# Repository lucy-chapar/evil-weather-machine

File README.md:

# Evil Weather Machine

A carrier PCB and new firmware for the [PrintKits Digital Sand kit](https://printkits.com/blogs/instructions/digital-sand):
an ESP32 DevKit, a GY-521 accelerometer, an 8x8 WS2812B panel and a 4xAA box in a printed cube.

| | |
|---|---|
| [`pcb/`](pcb/) | KiCad 7 two-layer board (52 × 59.5 mm) that replaces the kit's point-to-point wiring, with Gerbers ready to order |
| [`firmware/weather/`](firmware/weather/) | ESP32 firmware: today's weather plus an injection-day reminder, with WiFi setup from a phone and updates over WiFi |

## Firmware

The panel flips through the current temperature, an animated icon for the weather right now (the moon in
its current phase at night), today's high and low, and the chance of rain when rain is likely in the next
12 hours. On injection days it adds a beating trans-flag heart, with a green dot in the corner for the
side to use.

### Shot day

A reminder for injectable estradiol (HRT).

**Schedule**
- One injection every 3 days: 10 injections in any 30-day window.
- The site alternates between the left and right side of the abdomen.
- Shot days are calculated from the calendar. Nothing is logged on the device.

**Display**
- On a shot day, one extra screen is added to the rotation, after the rain chance.
- It shows a heart in trans flag colours (blue, pink, white), beating, with white sparkle pixels around it.
- A green 2×2 dot in the bottom-left or bottom-right corner marks the injection side: left or right.
- On other days the screen is not shown.

**Configuration** ([`config.h`](firmware/weather/src/config.h))
- `LAST_SHOT_YEAR`, `LAST_SHOT_MONTH`, `LAST_SHOT_DAY`: the date of one injection to count from.
- `LAST_SHOT_SIDE`: the side of that injection, `'L'` or `'R'`.
- `SHOT_EVERY_DAYS`: the interval, 3 by default.
- If an injection is taken on a different day, the schedule does not adjust by itself. Set the values
  above to the most recent injection and update the firmware.

**Timekeeping**
- The date comes from internet time (NTP), in the local timezone reported by the weather service.
- After the first successful connection, the timezone is stored and the count continues without WiFi.
  Internet time is still needed after each power cycle.

Quick start, with [PlatformIO](https://platformio.org/) installed:

```bash
cd firmware/weather
pio run -t upload          # first time, over USB
pio run -e ota -t upload   # after that, over WiFi
```

On first boot, join the `DigitalSand-Weather` WiFi network from a phone to connect the toy to your WiFi.
Settings (units, panel orientation, shot schedule) are in
[`firmware/weather/src/config.h`](firmware/weather/src/config.h). See the
[firmware README](firmware/weather/README.md) for details.

## PCB

The board carries the ESP32 (either 0.9 in or 1.0 in header spacing), the GY-521, the button and screw
terminals for the battery and the LED panel. It's generated by
[`pcb/tools/generate_kicad.py`](pcb/tools/generate_kicad.py); see the [PCB README](pcb/README.md) for
assembly notes and what to check before ordering. The board hasn't been fabricated yet.

## Tools

- KiCad 7, used through its bundled Python for the PCB generator.
- PlatformIO with `espressif32@6.4.0` for the firmware.
- `rsvg-convert` (librsvg) for the preview images.

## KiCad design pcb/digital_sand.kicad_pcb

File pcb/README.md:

# Digital Sand Toy – ESP32 carrier PCB

KiCad 7 project for a two-layer board that replaces the point-to-point wiring of the
[PrintKits Digital Sand kit](https://printkits.com/blogs/instructions/digital-sand).
It uses the same parts and the same connections; the board holds the parts and does the wiring.

## Files

| Path | Contents |
|---|---|
| `digital_sand.kicad_pro` | KiCad project (open this) |
| `digital_sand.kicad_sch` | Schematic ([PDF](docs/schematic.pdf)) |
| `digital_sand.kicad_pcb` | Board: 52 × 59.5 mm, 2 layers |
| `lib/` | Project symbols and footprints: ESP32 DevKit V1 30-pin, GY-521, `VBAT` power symbol |
| `docs/` | Schematic PDF and board previews |
| `fab/digital_sand_gerbers.zip` | Gerbers and Excellon drill files |
| `tools/generate_kicad.py` | Script that generates all of the above |

## Connections (same as the kit wiring diagram)

| ESP32 pin | Goes to |
|---|---|
| D5 (GPIO5) | J3 `DIN` → LED panel data in |
| D4 (GPIO4) | SW1 → GND |
| D21 (GPIO21) | GY-521 SDA |
| D22 (GPIO22) | GY-521 SCL |
| 3V3 | GY-521 VCC |
| VIN | `VBAT` rail (battery and LED panel 5 V) |
| GND | Common ground |

As in the original wiring, the 4×AA box (J1) feeds the LED panel's extra power wires (J2) directly.
The ESP32 runs from the same rail through VIN.

## Assembly

- **U1, ESP32 DevKit (30-pin)**: components up, USB connector towards the `USB` arrow at the board edge,
  antenna over the copper-free area marked `ANTENNA`.
  - The header row on the terminal-block side has two rows of holes. Use the outer row (`1.0in`) for
    boards with 25.4 mm between header rows, and the inner row (`0.9in`) for 22.86 mm boards.
  - Solder the board's header pins straight in, or fit 1×15 female headers to keep it removable.
- **U2, GY-521**: components up, square pad = VCC, module body over the board towards the bottom edge.
- **SW1**: the kit's 6 mm button. To use an external button instead, solder one wire to a pad on each side
  of the footprint (one `1` pad and one `2` pad).
- **J1–J3**: 3.5 mm pitch screw terminals with the wire openings facing the board edge.
  You can also solder wires straight into the holes.
  - J1 `BAT`: battery red → `+`, black → `-`
  - J2 `LED PWR`: the panel's extra red wire → `+`, white → `-`
  - J3 `LED IN`: panel input red → `5V`, white → `GND`, green → `DIN`
- **C1 (optional)**: 470–1000 µF electrolytic, rated 10 V or higher, `+` to the square pad.
- **H1–H4**: M3 mounting holes on a 45 × 52.5 mm grid.

## Check before ordering

- **ESP32 width.** Measure the header-to-header spacing on the board the kit ships with.
  The footprint takes 0.9 in and 1.0 in boards.
- **Accelerometer orientation.** The firmware reads gravity from the MPU-6050, and the stock firmware is
  a prebuilt ESPHome image. Mount the board so the GY-521 faces the same way relative to the LED matrix
  as in the original build, or the sand falls the wrong way. A tilt test before final mounting is the
  quickest check.
- **Enclosure.** The board is not matched to the printed case, so the case needs mounting points for it.

## Notes

- Unchanged from the kit: the LED panel runs straight off 4×AA. Fresh alkaline cells give up to about
  6.4 V, and WS2812B LEDs are rated to 5.3 V. NiMH cells (4.8 V) stay within that rating.
- Switch the battery off while the ESP32 is plugged into USB, because USB and the battery share the 5 V rail.
- Fabrication: 2 layers, 1.6 mm, 1 oz copper, 0.2 mm minimum track and space, 0.3 mm minimum drill.
  Any standard PCB service can make it from the zip.
- KiCad 7 cannot run ERC from the command line. Run Inspect → Electrical Rules Checker once in the
  schematic editor. Connectivity is checked by the generator against the kit wiring.

## Regenerating

`tools/generate_kicad.py` writes the libraries, schematic and board. It then checks the schematic netlist
against the kit wiring, fills the copper zones, runs DRC and re-exports `docs/` and `fab/`.
Run it with KiCad 7's bundled Python, which provides `pcbnew`:

```bash
/Applications/KiCad/KiCad.app/Contents/Frameworks/Python.framework/Versions/Current/bin/python3 tools/generate_kicad.py
```

The script overwrites the KiCad files. Once you start editing the design in KiCad itself, stop using the script.

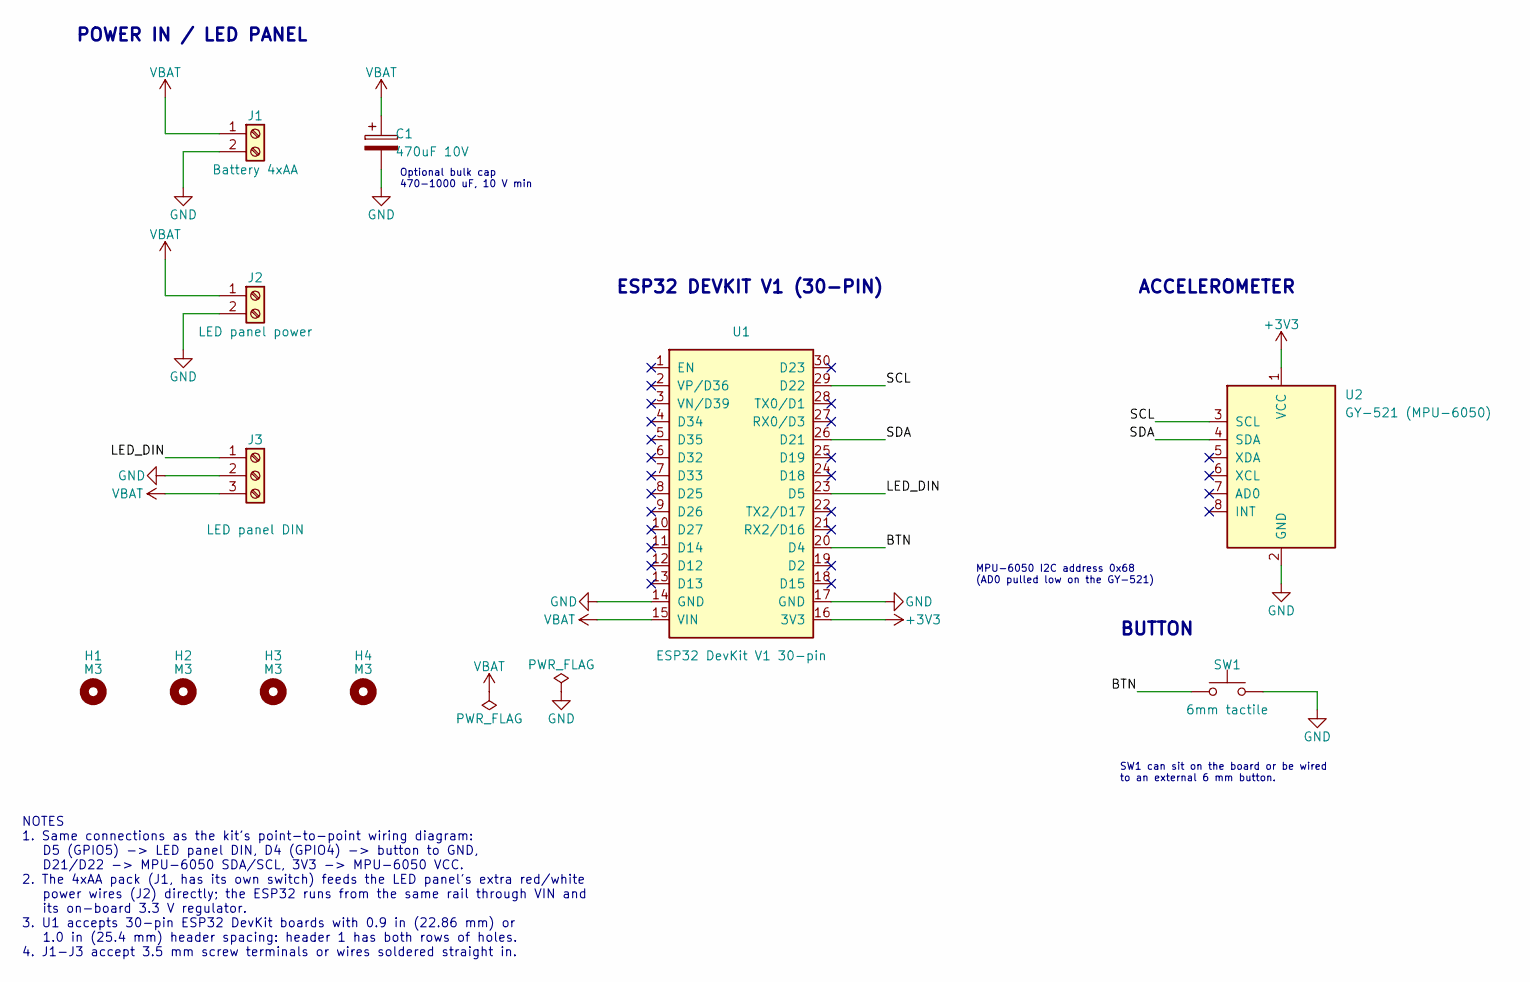
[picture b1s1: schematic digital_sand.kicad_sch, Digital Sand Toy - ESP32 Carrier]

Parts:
C1: 470uF 10V; CP_Radial_D8.0mm_P3.50mm
H1, H2, H3, H4: M3; MountingHole_3.2mm_M3
J1: Battery 4xAA; TerminalBlock_Phoenix_PT-1,5-2-3.5-H_1x02_P3.50mm_Horizontal
J2: LED panel power; TerminalBlock_Phoenix_PT-1,5-2-3.5-H_1x02_P3.50mm_Horizontal
J3: LED panel DIN; TerminalBlock_Phoenix_PT-1,5-3-3.5-H_1x03_P3.50mm_Horizontal
SW1: 6mm tactile; SW_PUSH_6mm
U1: ESP32 DevKit V1 30-pin; ESP32_DevKit_V1_30pin_DualRow
U2: GY-521 (MPU-6050); GY-521_MPU6050_Module

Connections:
+3V3: U1.16 (3V3), U2.1 (VCC)
/BTN: SW1.1, U1.20 (D4)
/LED_DIN: J3.1, U1.23 (D5)
/SCL: U1.29 (D22), U2.3 (SCL)
/SDA: U1.26 (D21), U2.4 (SDA)
GND: C1.2, J1.2, J2.2, J3.2, SW1.2, U1.14 (GND), U1.17 (GND), U2.2 (GND)
VBAT: C1.1, J1.1, J2.1, J3.3, U1.15 (VIN)

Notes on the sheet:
POWER IN / LED PANEL
ESP32 DEVKIT V1 (30-PIN)
ACCELEROMETER
BUTTON
Optional bulk cap 470-1000 uF, 10 V min
SW1 can sit on the board or be wired to an external 6 mm button.
MPU-6050 I2C address 0x68 (AD0 pulled low on the GY-521)
NOTES 1. Same connections as the kit's point-to-point wiring diagram: D5 (GPIO5) -> LED panel DIN, D4 (GPIO4) -> button to GND, D21/D22 -> MPU-6050 SDA/SCL, 3V3 -> MPU-6050 VCC. 2. The 4xAA pack (J1, has its own switch) feeds the LED panel's extra red/white power wires (J2) directly; the ESP32 runs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

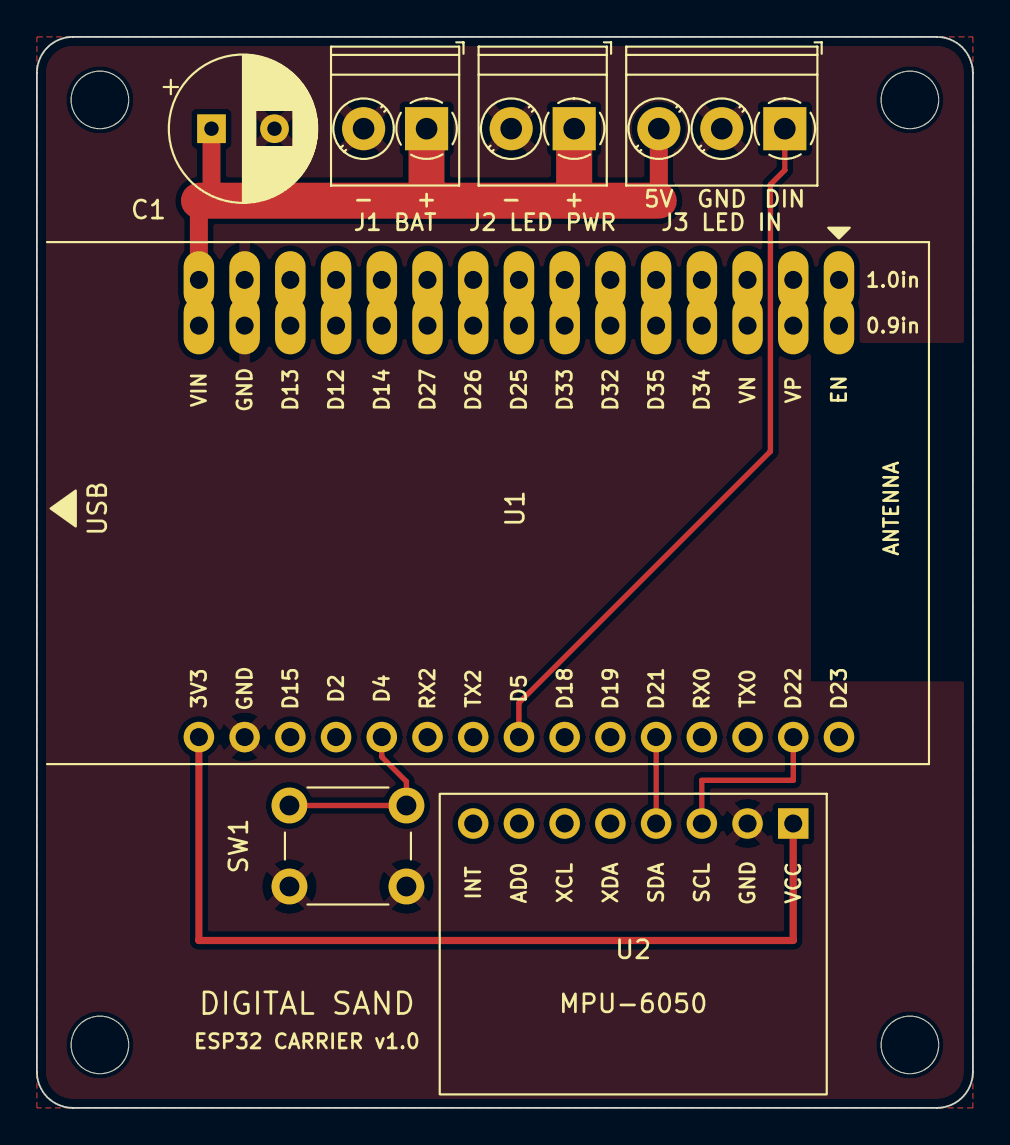
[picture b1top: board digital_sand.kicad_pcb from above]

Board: 2 copper layers, 52.0 x 59.5 mm, 11 parts (0 on the bottom side), 7 nets.
